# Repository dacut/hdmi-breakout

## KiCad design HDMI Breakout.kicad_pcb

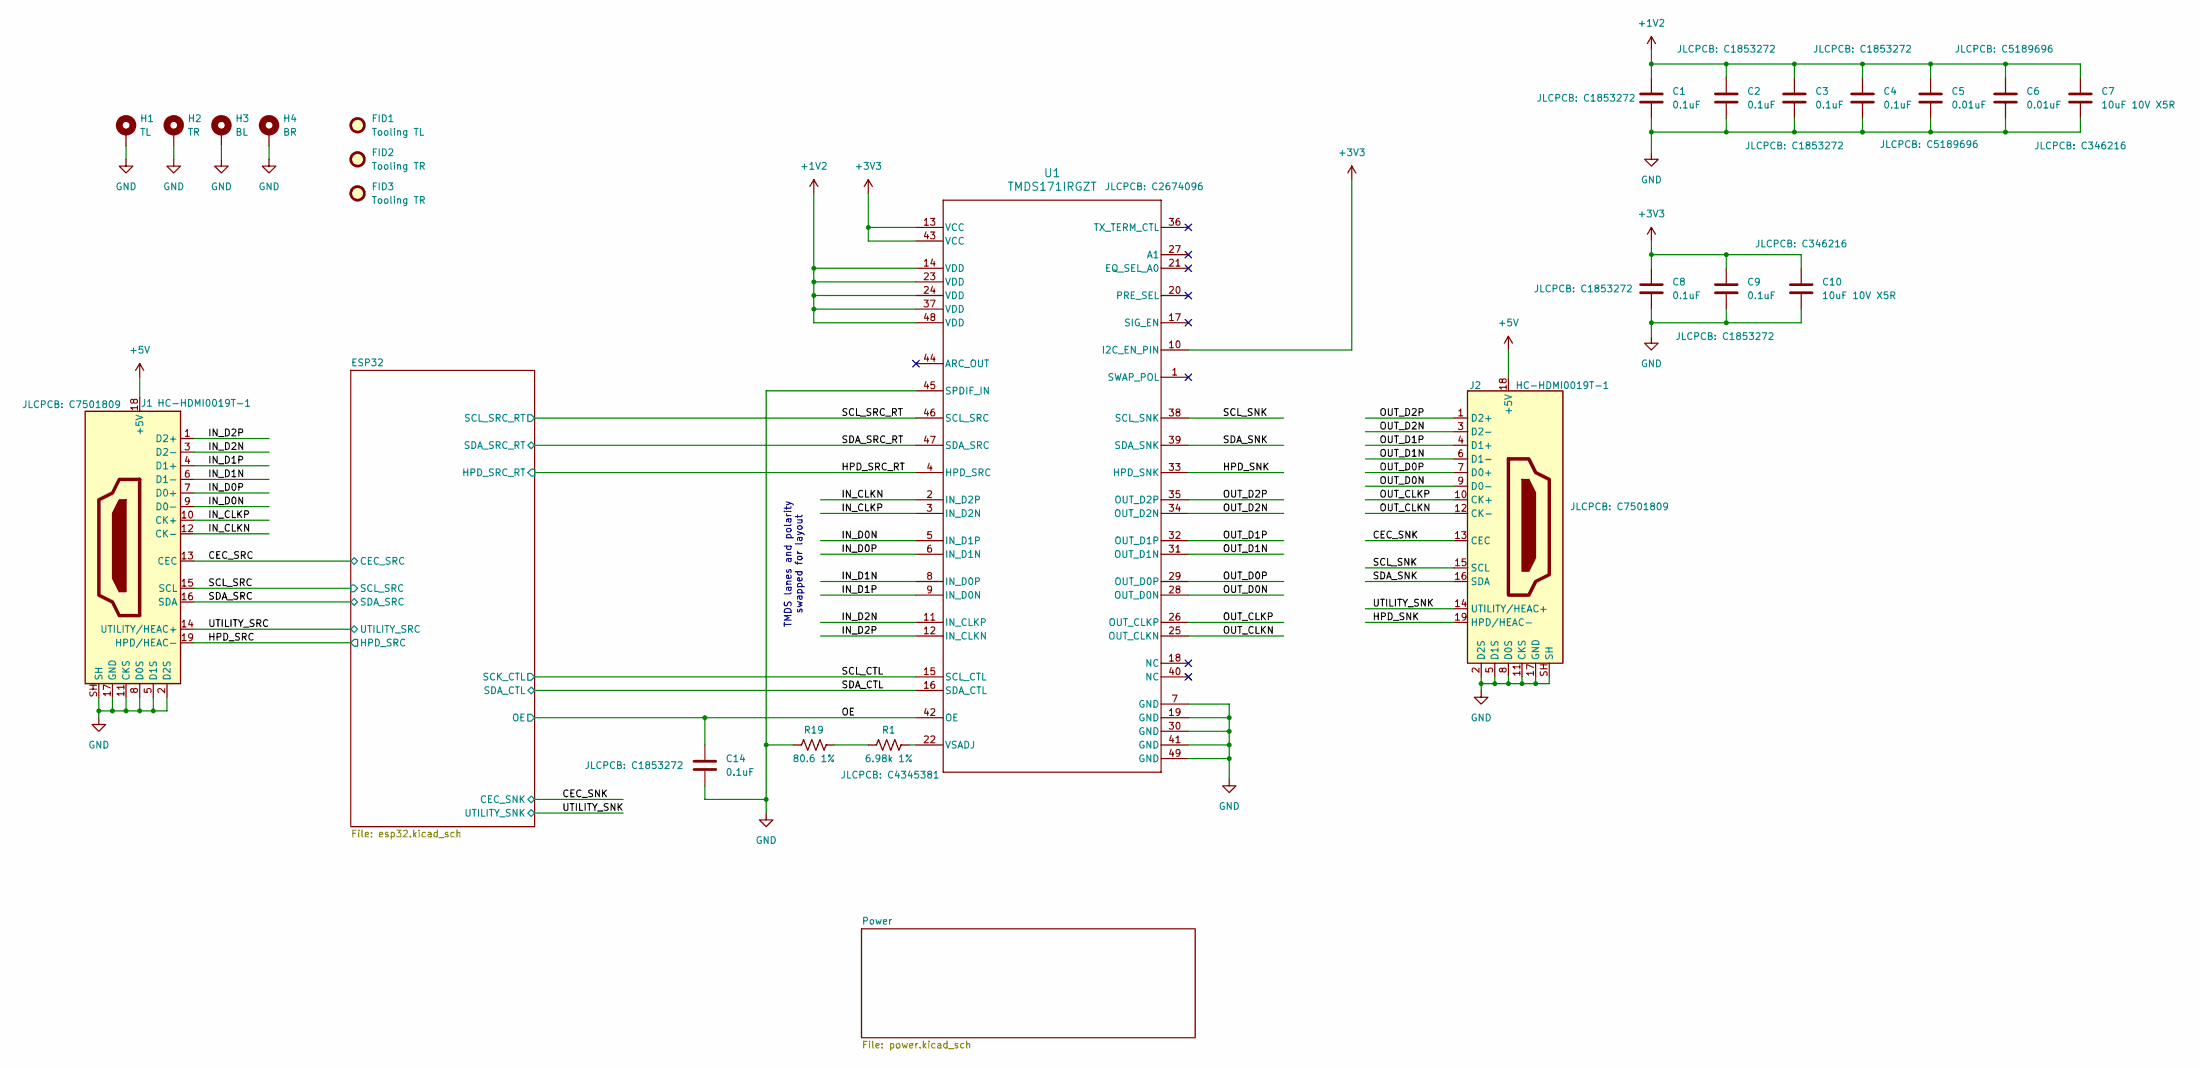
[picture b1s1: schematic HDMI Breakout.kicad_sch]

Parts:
C1, C2, C3, C4, C8, C9, C14: 0.1uF; C_0402_1005Metric; JLCPCB C1853272
C5, C6: 0.01uF; C_0402_1005Metric; JLCPCB C5189696
C7, C10: 10uF 10V X5R; C_0805_2012Metric; JLCPCB C346216
FID1: Tooling TL; Fiducial_JLCPCB
FID2, FID3: Tooling TR; Fiducial_JLCPCB
H1: TL; MountingHole_2.2mm_M2_Pad
H2: TR; MountingHole_2.2mm_M2_Pad
H3: BL; MountingHole_2.2mm_M2_Pad
H4: BR; MountingHole_2.2mm_M2_Pad
J1, J2: HC-HDMI0019T-1; JLCPCB C7501809
R1: 6.98k 1%; R_0402_1005Metric; JLCPCB C4345381
R19: 80.6 1%; R_0402_1005Metric
U1: TMDS171IRGZT; RGZ0048B_NV; JLCPCB C2674096

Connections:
+1V2: C1.1, C2.1, C3.1, C4.1, C5.1, C6.1, C7.1, U1.14 (VDD), U1.23 (VDD), U1.24 (VDD), U1.37 (VDD), U1.48 (VDD); also elsewhere on the board
+3V3: C8.1, C9.1, C10.1, U1.10 (I2C_EN_PIN), U1.13 (VCC), U1.43 (VCC); also elsewhere on the board
+5V: J1.18 (+5V), J2.18 (+5V); also elsewhere on the board
/CEC_SNK: J2.13 (CEC); also elsewhere on the board
/CEC_SRC: J1.13 (CEC); also elsewhere on the board
/HPD_SNK: J2.19 (HPD/HEAC-), U1.33 (HPD_SNK)
/HPD_SRC: J1.19 (HPD/HEAC-); also elsewhere on the board
/HPD_SRC_RT: U1.4 (HPD_SRC); also elsewhere on the board
/IN_CLKN: J1.12 (CK-), U1.2 (IN_D2P)
/IN_CLKP: J1.10 (CK+), U1.3 (IN_D2N)
/IN_D0N: J1.9 (D0-), U1.5 (IN_D1P)
/IN_D0P: J1.7 (D0+), U1.6 (IN_D1N)
/IN_D1N: J1.6 (D1-), U1.8 (IN_D0P)
/IN_D1P: J1.4 (D1+), U1.9 (IN_D0N)
/IN_D2N: J1.3 (D2-), U1.11 (IN_CLKP)
/IN_D2P: J1.1 (D2+), U1.12 (IN_CLKN)
/OE: C14.1, U1.42 (OE); also elsewhere on the board
/OUT_CLKN: J2.12 (CK-), U1.25 (OUT_CLKN)
/OUT_CLKP: J2.10 (CK+), U1.26 (OUT_CLKP)
/OUT_D0N: J2.9 (D0-), U1.28 (OUT_D0N)
/OUT_D0P: J2.7 (D0+), U1.29 (OUT_D0P)
/OUT_D1N: J2.6 (D1-), U1.31 (OUT_D1N)
/OUT_D1P: J2.4 (D1+), U1.32 (OUT_D1P)
/OUT_D2N: J2.3 (D2-), U1.34 (OUT_D2N)
/OUT_D2P: J2.1 (D2+), U1.35 (OUT_D2P)
/SCL_CTL: U1.15 (SCL_CTL); also elsewhere on the board
/SCL_SNK: J2.15 (SCL), U1.38 (SCL_SNK)
/SCL_SRC: J1.15 (SCL); also elsewhere on the board
/SCL_SRC_RT: U1.46 (SCL_SRC); also elsewhere on the board
/SDA_CTL: U1.16 (SDA_CTL); also elsewhere on the board
/SDA_SNK: J2.16 (SDA), U1.39 (SDA_SNK)
/SDA_SRC: J1.16 (SDA); also elsewhere on the board
/SDA_SRC_RT: U1.47 (SDA_SRC); also elsewhere on the board
/UTILITY_SNK: J2.14 (UTILITY/HEAC+); also elsewhere on the board
/UTILITY_SRC: J1.14 (UTILITY/HEAC+); also elsewhere on the board
GND: C1.2, C2.2, C3.2, C4.2, C5.2, C6.2, C7.2, C8.2, C9.2, C10.2, C14.2, H1.1, H2.1, H3.1, H4.1, J1.2 (D2S), J1.5 (D1S), J1.8 (D0S), J1.11 (CKS), J1.17 (GND), J1.SH, J2.2 (D2S), J2.5 (D1S), J2.8 (D0S), J2.11 (CKS), J2.17 (GND), J2.SH, R19.1, U1.7 (GND), U1.19 (GND), U1.30 (GND), U1.41 (GND), U1.45 (SPDIF_IN), U1.49 (GND); also elsewhere on the board
unnamed: R1.1, R19.2
unnamed: R1.2, U1.22 (VSADJ)

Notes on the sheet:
TMDS lanes and polarity swapped for layout

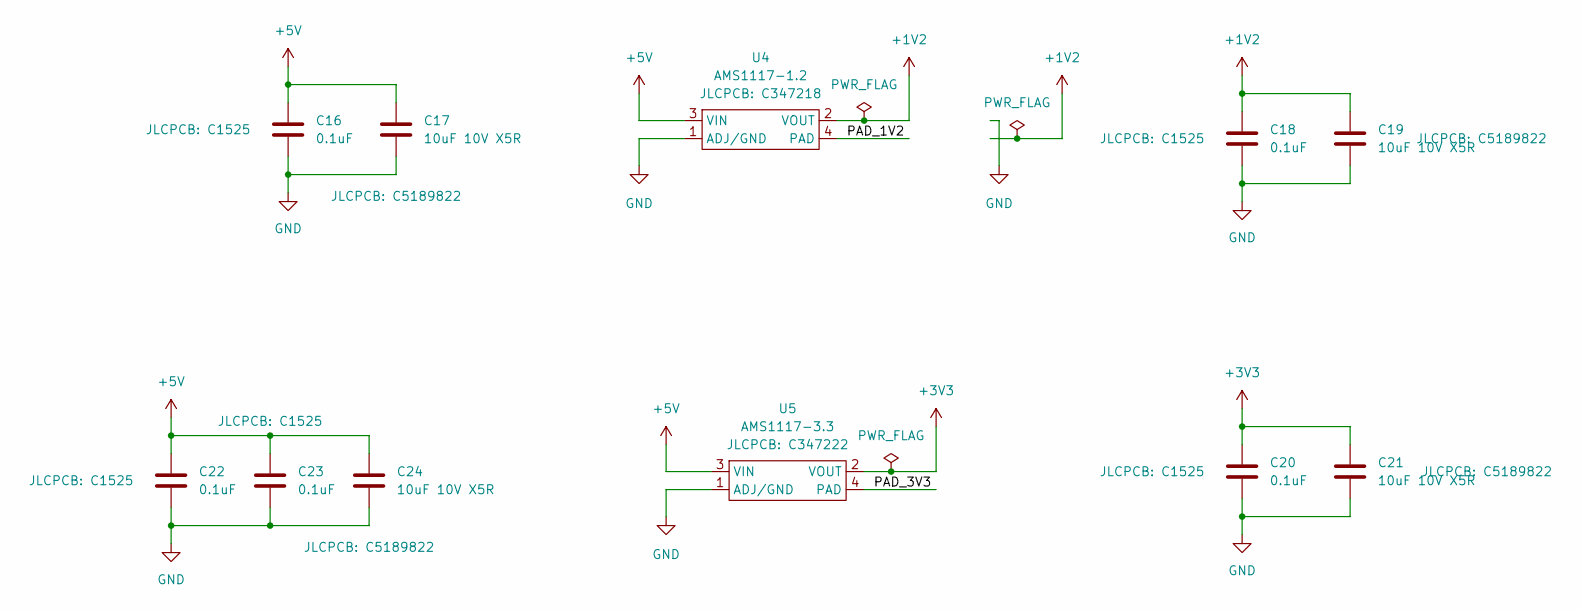
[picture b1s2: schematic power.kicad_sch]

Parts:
C16, C18, C20, C22, C23: 0.1uF; C_0402_1005Metric; JLCPCB C1525
C17, C19, C21, C24: 10uF 10V X5R; C_0805_2012Metric; JLCPCB C5189822
U4: AMS1117-1.2; SOT-223; JLCPCB C347218
U5: AMS1117-3.3; SOT-223; JLCPCB C347222

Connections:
+1V2: C18.1, C19.1, U4.2 (VOUT); also elsewhere on the board
+3V3: C20.1, C21.1, U5.2 (VOUT); also elsewhere on the board
+5V: C16.1, C17.1, C22.1, C23.1, C24.1, U4.3 (VIN), U5.3 (VIN); also elsewhere on the board
/Power/PAD_1V2: U4.4 (PAD)
/Power/PAD_3V3: U5.4 (PAD)
GND: C16.2, C17.2, C18.2, C19.2, C20.2, C21.2, C22.2, C23.2, C24.2, U4.1 (ADJ/GND), U5.1 (ADJ/GND); also elsewhere on the board

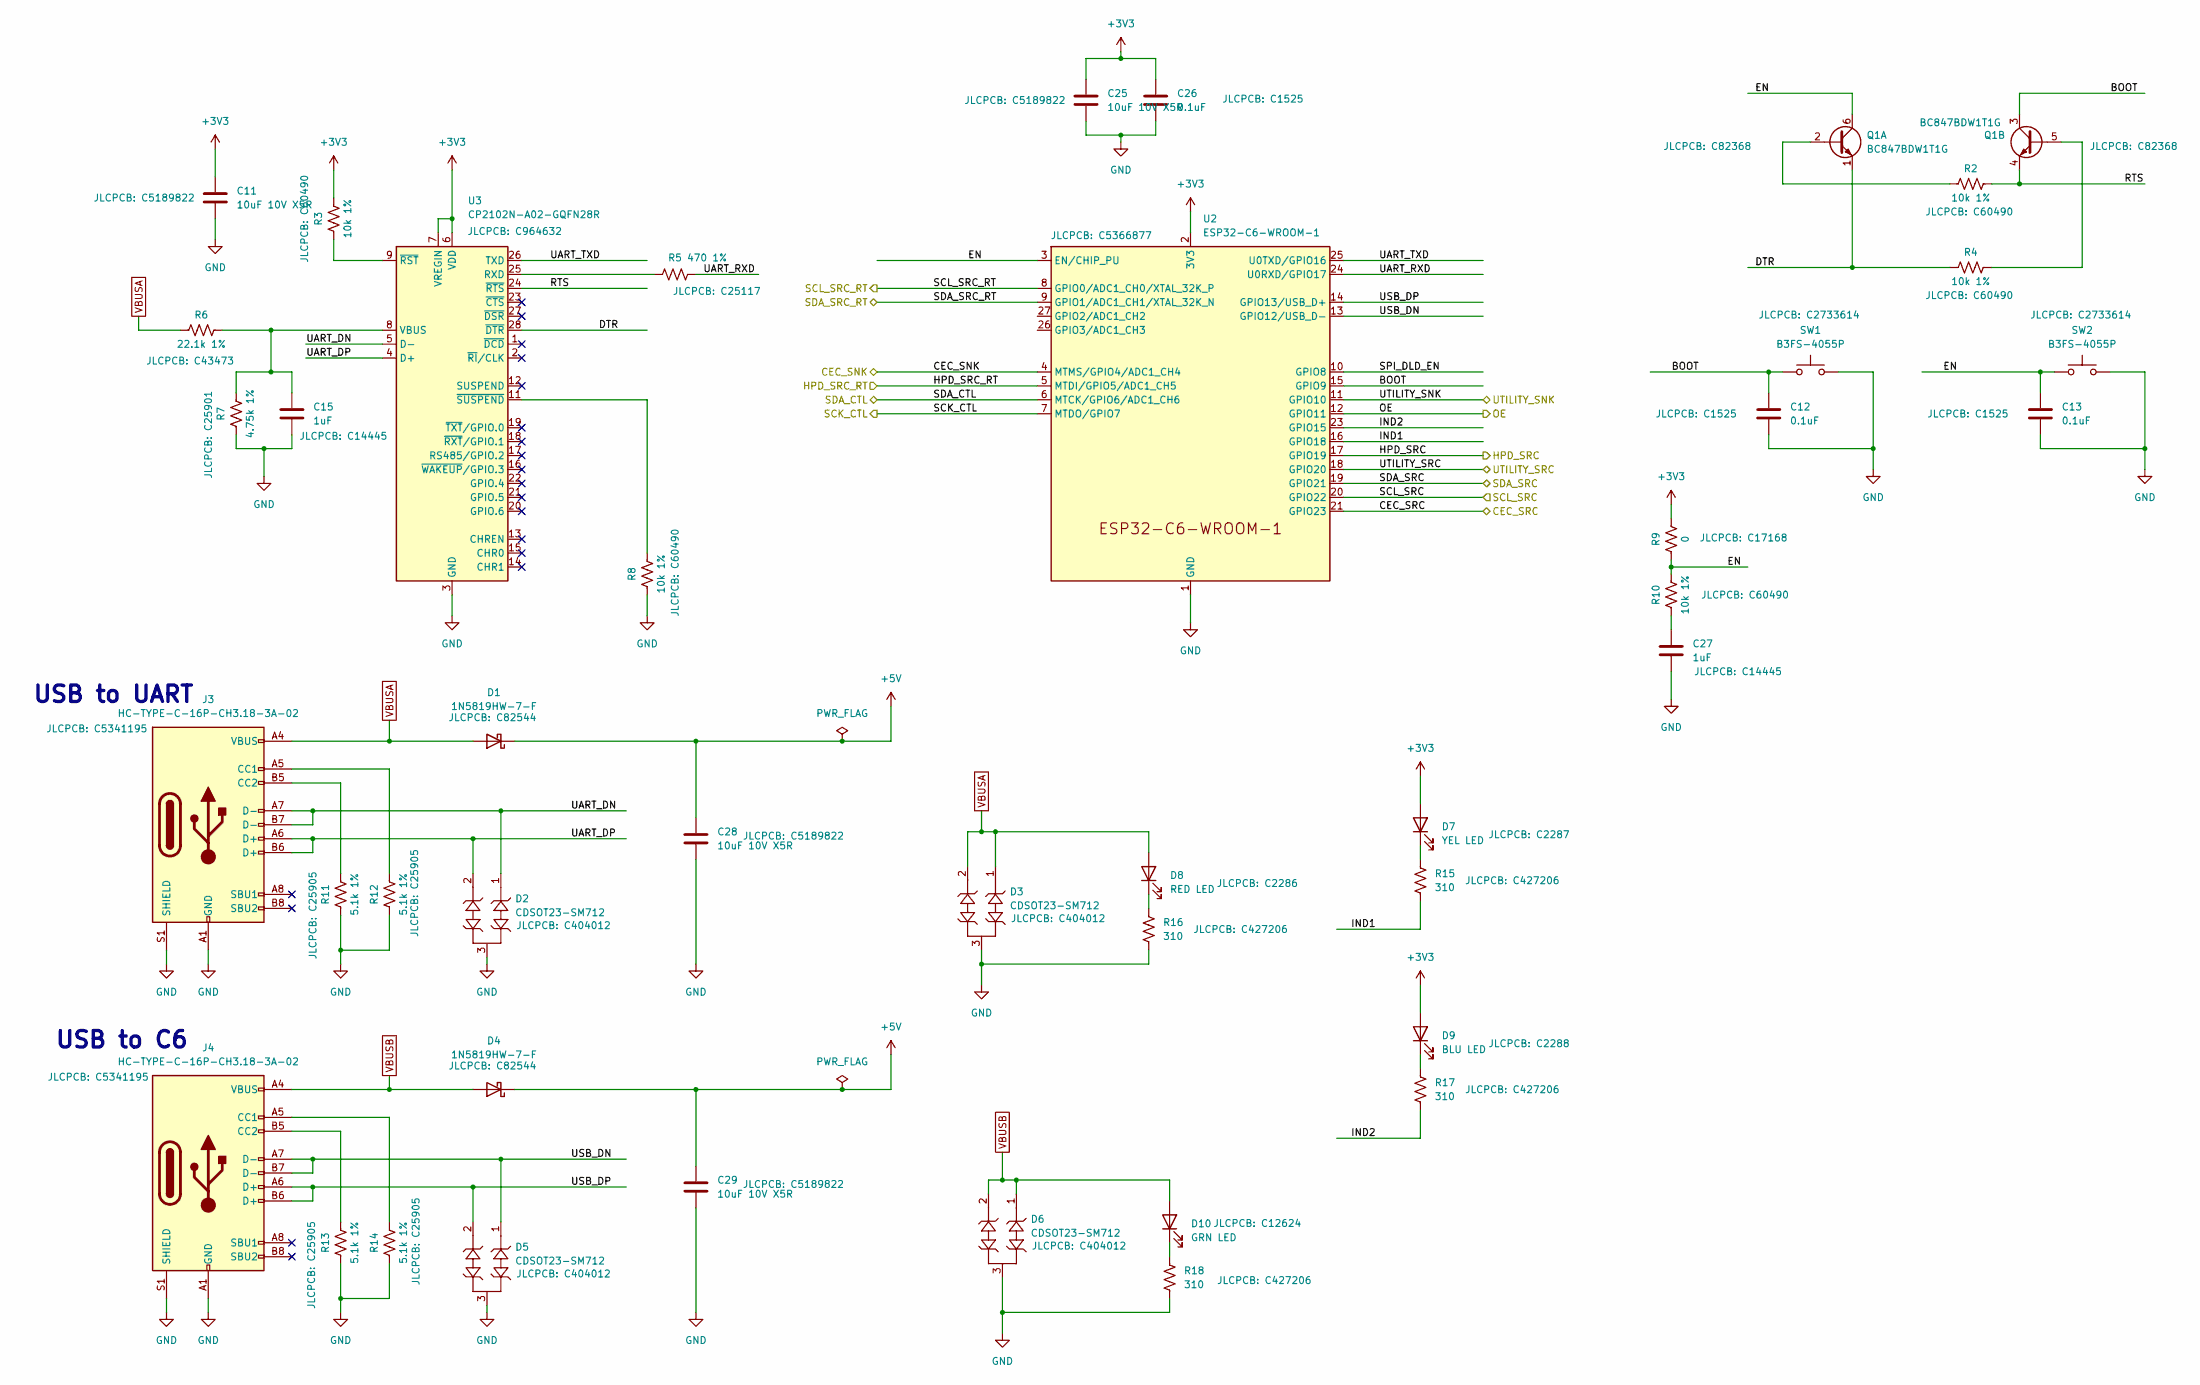
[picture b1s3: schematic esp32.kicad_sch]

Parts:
C11, C25, C28, C29: 10uF 10V X5R; C_0805_2012Metric; JLCPCB C5189822
C12, C13, C26: 0.1uF; C_0402_1005Metric; JLCPCB C1525
C15, C27: 1uF; C_0402_1005Metric; JLCPCB C14445
D1, D4: 1N5819HW-7-F; D_SOD-123; JLCPCB C82544
D2, D3, D5, D6: CDSOT23-SM712; SOT-23; JLCPCB C404012
D7: YEL LED; LED_0603_1608Metric; JLCPCB C2287
D8: RED LED; LED_0603_1608Metric; JLCPCB C2286
D9: BLU LED; LED_0603_1608Metric; JLCPCB C2288
D10: GRN LED; LED_0603_1608Metric; JLCPCB C12624
J3, J4: HC-TYPE-C-16P-CH3.18-3A-02; USB_C_Receptacle_HCTL_HC-TYPE-C-16P-01A; JLCPCB C5341195
Q1: BC847BDW1T1G; SOT-363_SC-70-6; JLCPCB C82368
R2, R3, R4, R8, R10: 10k 1%; R_0402_1005Metric; JLCPCB C60490
R5: 470 1%; R_0402_1005Metric; JLCPCB C25117
R6: 22.1k 1%; R_0402_1005Metric; JLCPCB C43473
R7: 4.75k 1%; R_0402_1005Metric; JLCPCB C25901
R9: 0; R_0402_1005Metric; JLCPCB C17168
R11, R12, R13, R14: 5.1k 1%; R_0402_1005Metric; JLCPCB C25905
R15, R16, R17, R18: 310; R_0402_1005Metric; JLCPCB C427206
SW1, SW2: B3FS-4055P; SW_SPST_Omron_B3FS-4000; JLCPCB C2733614
U2: ESP32-C6-WROOM-1; JLCPCB C5366877
U3: CP2102N-A02-GQFN28R; QFN-28-1EP_5x5mm_P0.5mm_EP3.35x3.35mm; JLCPCB C964632

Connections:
+3V3: C11.1, C25.1, C26.1, D7.2 (A), D9.2 (A), R3.2, R9.2, U2.2 (3V3), U3.6 (VDD), U3.7 (VREGIN); also elsewhere on the board
+5V: C28.1, C29.1, D1.1 (K), D4.1 (K); also elsewhere on the board
/CEC_SNK: U2.4 (MTMS/GPIO4/ADC1_CH4); also elsewhere on the board
/CEC_SRC: U2.21 (GPIO23); also elsewhere on the board
/ESP32/BOOT: C12.1, Q1.3 (C2), SW1.1, U2.15 (GPIO9)
/ESP32/DTR: Q1.1 (E1), R4.1, U3.28 (~DTR)
/ESP32/EN: C13.1, Q1.6 (C1), R9.1, R10.2, SW2.1, U2.3 (EN/CHIP_PU)
/ESP32/IND1: R15.2, U2.16 (GPIO18)
/ESP32/IND2: R17.2, U2.23 (GPIO15)
/ESP32/RTS: Q1.4 (E2), R2.2, U3.24 (~RTS)
/ESP32/SPI_DLD_EN: U2.10 (GPIO8)
/ESP32/UART_DN: D2.1, J3.A7 (D-), J3.B7 (D-), U3.5 (D-)
/ESP32/UART_DP: D2.2, J3.A6 (D+), J3.B6 (D+), U3.4 (D+)
/ESP32/UART_RXD: R5.2, U2.24 (U0RXD/GPIO17)
/ESP32/UART_TXD: U2.25 (U0TXD/GPIO16), U3.26 (TXD)
/ESP32/USB_DN: D5.1, J4.A7 (D-), J4.B7 (D-), U2.13 (GPIO12/USB_D-)
/ESP32/USB_DP: D5.2, J4.A6 (D+), J4.B6 (D+), U2.14 (GPIO13/USB_D+)
/HPD_SRC: U2.17 (GPIO19); also elsewhere on the board
/HPD_SRC_RT: U2.5 (MTDI/GPIO5/ADC1_CH5); also elsewhere on the board
/OE: U2.12 (GPIO11); also elsewhere on the board
/SCL_CTL: U2.7 (MTDO/GPIO7); also elsewhere on the board
/SCL_SRC: U2.20 (GPIO22); also elsewhere on the board
/SCL_SRC_RT: U2.8 (GPIO0/ADC1_CH0/XTAL_32K_P); also elsewhere on the board
/SDA_CTL: U2.6 (MTCK/GPIO6/ADC1_CH6); also elsewhere on the board
/SDA_SRC: U2.19 (GPIO21); also elsewhere on the board
/SDA_SRC_RT: U2.9 (GPIO1/ADC1_CH1/XTAL_32K_N); also elsewhere on the board
/UTILITY_SNK: U2.11 (GPIO10); also elsewhere on the board
/UTILITY_SRC: U2.18 (GPIO20); also elsewhere on the board
GND: C11.2, C12.2, C13.2, C15.2, C25.2, C26.2, C27.2, C28.2, C29.2, D2.3, D3.3, D5.3, D6.3, J3.A1 (GND), J3.A12 (GND), J3.B1 (GND), J3.B12 (GND), J3.S1 (SHIELD), J4.A1 (GND), J4.A12 (GND), J4.B1 (GND), J4.B12 (GND), J4.S1 (SHIELD), R7.1, R8.1, R11.1, R12.1, R13.1, R14.1, R16.2, R18.2, SW1.2, SW2.2, U2.1 (GND), U2.28 (GND), U2.29 (GND), U3.3 (GND), U3.29 (GND); also elsewhere on the board
unnamed: C27.1, R10.1
unnamed: D7.1 (K), R15.1
unnamed: D8.1 (K), R16.1
unnamed: D9.1 (K), R17.1
unnamed: D10.1 (K), R18.1
unnamed: J3.A5 (CC1), R12.2
unnamed: J3.B5 (CC2), R11.2
unnamed: J4.A5 (CC1), R14.2
unnamed: J4.B5 (CC2), R13.2
unnamed: Q1.2 (B1), R2.1
unnamed: Q1.5 (B2), R4.2
unnamed: R5.1, U3.25 (RXD)
unnamed: C15.1, R6.2, R7.2, U3.8 (VBUS)
unnamed: R3.1, U3.9 (~RST)
unnamed: R8.2, U3.11 (~SUSPEND)
VBUSA: D1.2 (A), D3.1, D3.2, D8.2 (A), J3.A4 (VBUS), J3.A9 (VBUS), J3.B4 (VBUS), J3.B9 (VBUS), R6.1
VBUSB: D4.2 (A), D6.1, D6.2, D10.2 (A), J4.A4 (VBUS), J4.A9 (VBUS), J4.B4 (VBUS), J4.B9 (VBUS)

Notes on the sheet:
USB to C6
USB to UART

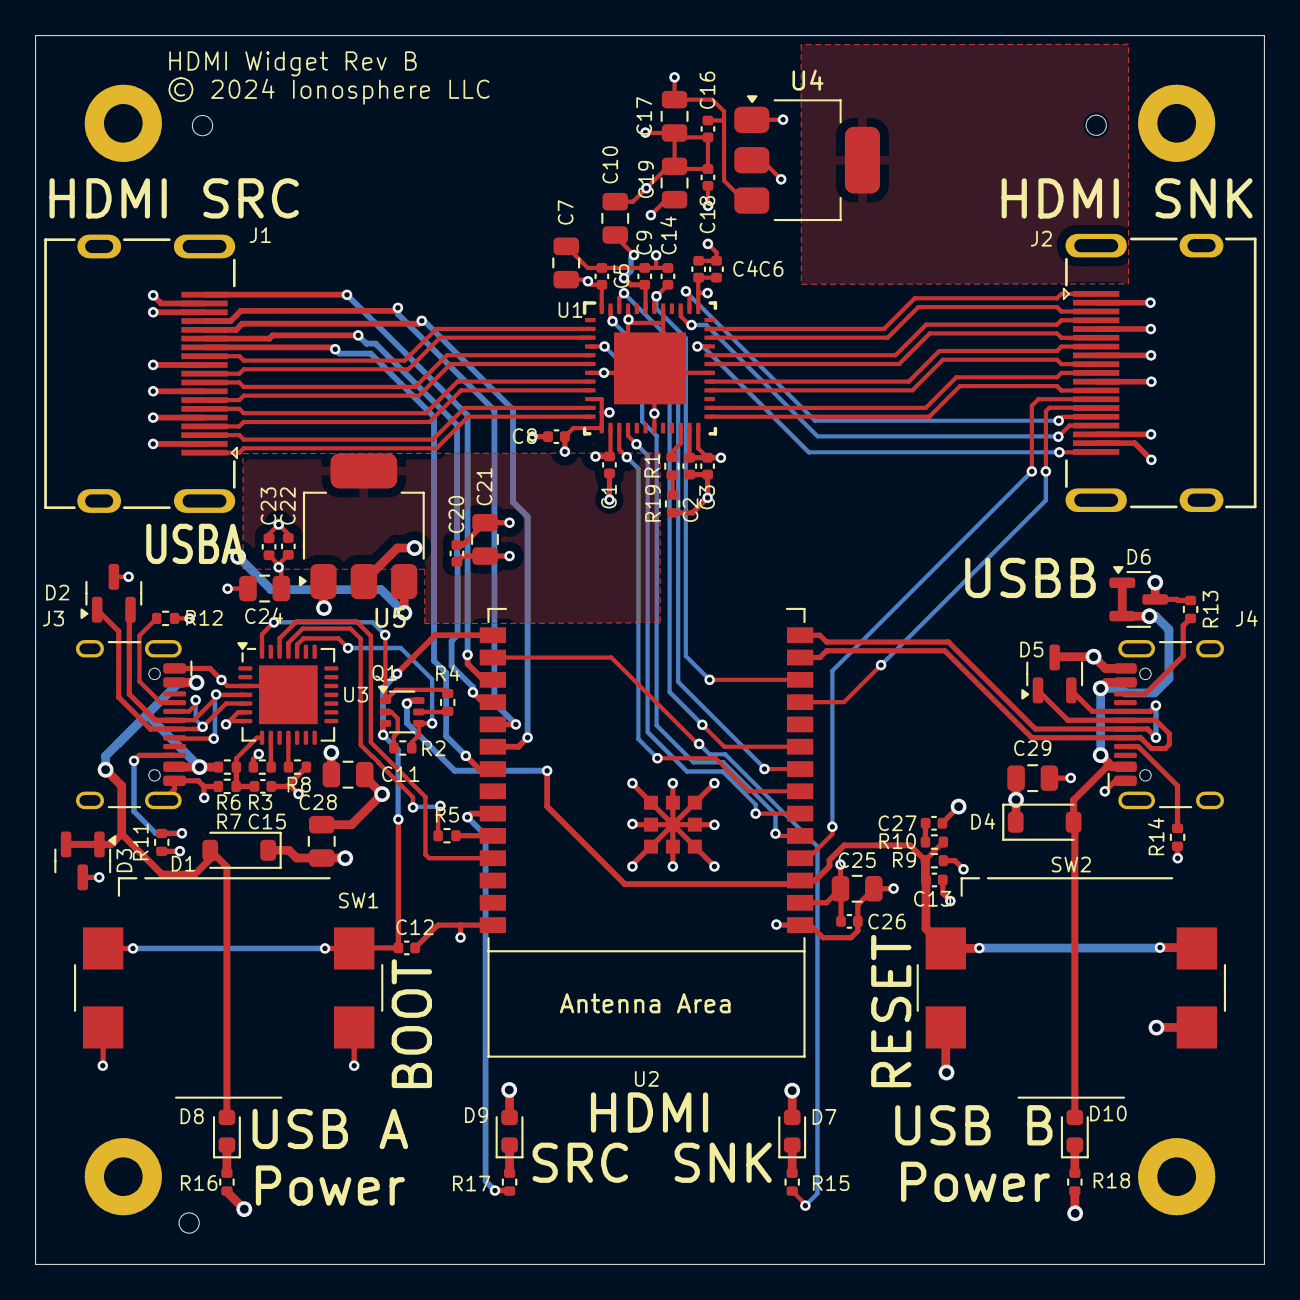
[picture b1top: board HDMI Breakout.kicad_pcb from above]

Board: 4 copper layers, 70.0 x 70.0 mm, 77 parts (0 on the bottom side), 67 nets.

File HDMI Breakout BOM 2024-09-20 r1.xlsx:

Designator | Value | Footprint | Qty | JLCPCB Part # |  | Description
C1,C2,C3,C4,C8,C9,C12,C13,C14,C16,C18,C20,C22,C23,C26 | 0.1uF | Capacitor_SMD:C_0402_1005Metric | 15 | C1853272 |  | Unpolarized capacitor
C5,C6 | 0.01uF | Capacitor_SMD:C_0402_1005Metric | 2 | C5189696 |  | Unpolarized capacitor
C7,C10,C11,C17,C19,C21,C24,C25,C28,C29 | 10uF 10V X5R | Capacitor_SMD:C_0805_2012Metric | 10 | C5189822 |  | Unpolarized capacitor
C15,C27 | 1uF | Capacitor_SMD:C_0402_1005Metric | 2 | C1852899 |  | Unpolarized capacitor
D1,D4 | 1N5819HW-7-F | Diode_SMD:D_SOD-123 | 2 | C82544 |  | 40V 1A Schottky Barrier Rectifier Diode, DO-41
D2,D3,D5,D6 | CDSOT23-SM712 | Package_TO_SOT_SMD:SOT-23 | 4 | C404012 |  | Surface Mount TVS Diode
D7 | YEL LED | LED_SMD:LED_0603_1608Metric | 1 | C2287 |  | Light emitting diode
D8 | RED LED | LED_SMD:LED_0603_1608Metric | 1 | C2286 |  | Light emitting diode
D9 | BLU LED | LED_SMD:LED_0603_1608Metric | 1 | C2288 |  | Light emitting diode
D10 | GRN LED | LED_SMD:LED_0603_1608Metric | 1 | C12624 |  | Light emitting diode
J1,J2 | HC-HDMI0019T-1 | HDMI Breakout:HC-HDMI0019T-1 | 2 | C7501809 |  | HDMI A Connector
J3,J4 | HC-TYPE-C-16P-CH3.18-3A-02 | Connector_USB:USB_C_Receptacle_HCTL_HC-TYPE-C-16P-01A | 2 | C5341195 |  | USB 2.0-only 16P Type-C Receptacle connector
Q1 | BC847BDW1T1G | Package_TO_SOT_SMD:SOT-363_SC-70-6 | 1 | C82368 |  | 100mA IC, 45V Vce, Dual NPN/NPN Transistors, SOT-363
R1 | 6.98k 1% | Resistor_SMD:R_0402_1005Metric | 1 | C47500 |  | Resistor, US symbol
R2,R3,R4,R8,R10 | 10k 1% | Resistor_SMD:R_0402_1005Metric | 5 | C4275117 | C60490 | Resistor, US symbol
R5 | 470 1% | Resistor_SMD:R_0402_1005Metric | 1 | C4161303 | C25117 | Resistor, US symbol
R6 | 22.1k 1% | Resistor_SMD:R_0402_1005Metric | 1 | C43473 |  | Resistor, US symbol
R7 | 4.75k 1% | Resistor_SMD:R_0402_1005Metric | 1 | C25901 |  | Resistor, US symbol
R9 | 0 | Resistor_SMD:R_0402_1005Metric | 1 | C6649868 | C17168 | Resistor, US symbol
R11,R12,R13,R14 | 5.1k 1% | Resistor_SMD:R_0402_1005Metric | 4 | C2131849 | C25905 | Resistor, US symbol
R15,R16,R17,R18 | 310 | Resistor_SMD:R_0402_1005Metric | 4 | C427206 |  | Resistor, US symbol
R19 | 80.6 1% | Resistor_SMD:R_0402_1005Metric | 1 | C25134 |  | Resistor, US symbol
SW1,SW2 | B3FS-4055P | HDMI Breakout:SW_SPST_Omron_B3FS-4000 | 2 | C2733614 |  | Omron B3FS 6x6mm single pole normally-open tactile switch
U1 | TMDS171IRGZT | HDMI Breakout:RGZ0048B_NV | 1 | C2674096
U2 | ESP32-C6-WROOM-1 | PCM_Espressif:ESP32-C6-WROOM-1 | 1 | C5366877 |  | ESP32-C6-WROOM-1/U is a module that supports 2.4 GHz Wi-Fi 6 (802.11 ax), Bluet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
U3 | CP2102N-A02-GQFN28R | Package_DFN_QFN:QFN-28-1EP_5x5mm_P0.5mm_EP3.35x3.35mm | 1 | C964632 |  | USB to UART master bridge, QFN-28
U4 | AP2114HA-1.2TRG1 | Package_TO_SOT_SMD:SOT-223 | 1 | C3751555
U5 | AP2114HA-3.3TRG1 | Package_TO_SOT_SMD:SOT-223 | 1 | C460314

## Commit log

2024-09-03 Checkpoint before modifying JLCPCB part numbers.
2024-09-06 Before fixup2
2024-09-21 Update before DFM changes
2024-10-12 Remove(-ish) backup ZIP files
    Yeah, I know this won't be deleted from the Git history, but at least
    it de-pollutes the working directory.
2024-10-12 Ignore CAM directory.
2024-10-12 Checkpointing before moving to 1206 components

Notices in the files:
HDMI Breakout.kicad_pcb:
© 2024 Ionosphere LLC
